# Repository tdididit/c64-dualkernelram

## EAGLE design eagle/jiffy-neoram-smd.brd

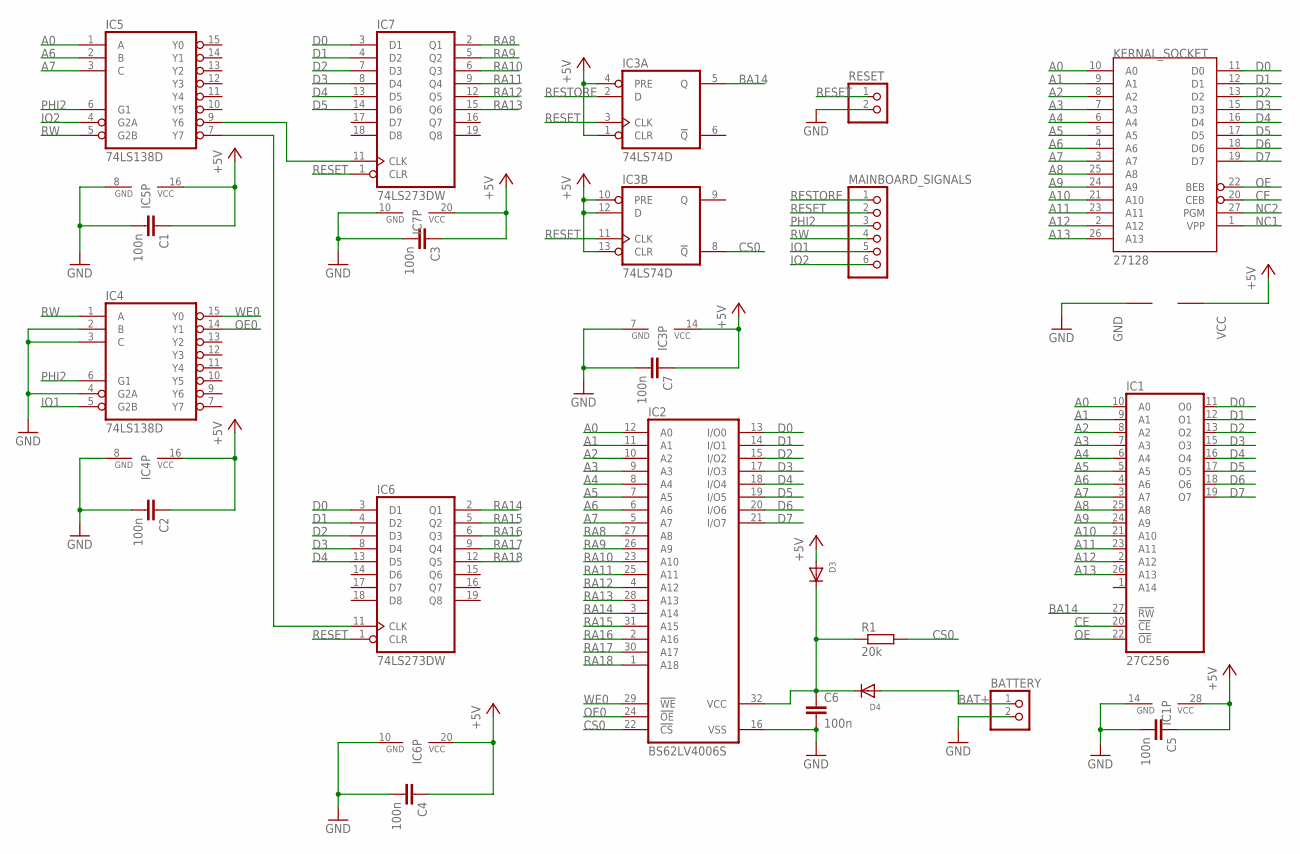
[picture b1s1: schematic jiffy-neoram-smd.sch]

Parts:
BATTERY: HEADER-1X2ROUND; 1X02_ROUND
C1, C2, C3, C4, C5, C6, C7: 100n; C0603
D3, D4: DIODESOD-323F; SOD-323F
IC1: 27C256; DIL28
IC2: BS62LV4006S; SOP-32
IC3: 74LS74D; SO14
IC4, IC5: 74LS138D; SO16
IC6, IC7: 74LS273DW; SO20W
KERNAL_SOCKET: DIL28-6
MAINBOARD_SIGNALS: HEADER-1X6ROUND; 1X06_ROUND
R1: 20k; R0603
RESET: HEADER-1X2ROUND; 1X02_ROUND

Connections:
+5V: C1.1, C2.1, C3.1, C4.1, C5.1, C7.1, D3.A, IC1.28 (VCC), IC3.1 (CLR), IC3.4 (PRE), IC3.10 (PRE), IC3.12 (D), IC3.13 (CLR), IC3.14 (VCC), IC4.16 (VCC), IC5.16 (VCC), IC6.20 (VCC), IC7.20 (VCC), KERNAL_SOCKET.28 (VCC)
A0: IC1.10 (A0), IC2.12 (A0), IC5.1 (A), KERNAL_SOCKET.10 (A0)
A1: IC1.9 (A1), IC2.11 (A1), KERNAL_SOCKET.9 (A1)
A2: IC1.8 (A2), IC2.10 (A2), KERNAL_SOCKET.8 (A2)
A3: IC1.7 (A3), IC2.9 (A3), KERNAL_SOCKET.7 (A3)
A4: IC1.6 (A4), IC2.8 (A4), KERNAL_SOCKET.6 (A4)
A5: IC1.5 (A5), IC2.7 (A5), KERNAL_SOCKET.5 (A5)
A6: IC1.4 (A6), IC2.6 (A6), IC5.2 (B), KERNAL_SOCKET.4 (A6)
A7: IC1.3 (A7), IC2.5 (A7), IC5.3 (C), KERNAL_SOCKET.3 (A7)
A8: IC1.25 (A8), KERNAL_SOCKET.25 (A8)
A9: IC1.24 (A9), KERNAL_SOCKET.24 (A9)
A10: IC1.21 (A10), KERNAL_SOCKET.21 (A10)
A11: IC1.23 (A11), KERNAL_SOCKET.23 (A11)
A12: IC1.2 (A12), KERNAL_SOCKET.2 (A12)
A13: IC1.26 (A13), KERNAL_SOCKET.26 (A13)
BA14: IC1.27 (!RW), IC3.5 (Q)
BAT+: BATTERY.1, D4.A
CE: IC1.20 (!CE), KERNAL_SOCKET.20 (CEB)
CS0: IC2.22 (!CS), IC3.8 (!Q), R1.2
D0: IC1.11 (O0), IC2.13 (I/O0), IC6.3 (D1), IC7.3 (D1), KERNAL_SOCKET.11 (D0)
D1: IC1.12 (O1), IC2.14 (I/O1), IC6.4 (D2), IC7.4 (D2), KERNAL_SOCKET.12 (D1)
D2: IC1.13 (O2), IC2.15 (I/O2), IC6.7 (D3), IC7.7 (D3), KERNAL_SOCKET.13 (D2)
D3: IC1.15 (O3), IC2.17 (I/O3), IC6.8 (D4), IC7.8 (D4), KERNAL_SOCKET.15 (D3)
D4: IC1.16 (O4), IC2.18 (I/O4), IC6.13 (D5), IC7.13 (D5), KERNAL_SOCKET.16 (D4)
D5: IC1.17 (O5), IC2.19 (I/O5), IC7.14 (D6), KERNAL_SOCKET.17 (D5)
D6: IC1.18 (O6), IC2.20 (I/O6), KERNAL_SOCKET.18 (D6)
D7: IC1.19 (O7), IC2.21 (I/O7), KERNAL_SOCKET.19 (D7)
GND: BATTERY.2, C1.2, C2.2, C3.2, C4.2, C5.2, C6.2, C7.2, IC1.14 (GND), IC2.16 (VSS), IC3.7 (GND), IC4.2 (B), IC4.3 (C), IC4.4 (G2A), IC4.8 (GND), IC5.8 (GND), IC6.10 (GND), IC7.10 (GND), KERNAL_SOCKET.14 (GND), RESET.2
IO1: IC4.5 (G2B), MAINBOARD_SIGNALS.5
IO2: IC5.4 (G2A), MAINBOARD_SIGNALS.6
unnamed: IC5.9 (Y6), IC7.11 (CLK)
unnamed: IC5.7 (Y7), IC6.11 (CLK)
unnamed: C6.1, D3.C, D4.C, IC2.32 (VCC), R1.1
NC1: KERNAL_SOCKET.1 (VPP)
NC2: KERNAL_SOCKET.27 (PGM)
OE: IC1.22 (!OE), KERNAL_SOCKET.22 (BEB)
OE0: IC2.24 (!OE), IC4.14 (Y1)
PHI2: IC4.6 (G1), IC5.6 (G1), MAINBOARD_SIGNALS.3
RA8: IC2.27 (A8), IC7.2 (Q1)
RA9: IC2.26 (A9), IC7.5 (Q2)
RA10: IC2.23 (A10), IC7.6 (Q3)
RA11: IC2.25 (A11), IC7.9 (Q4)
RA12: IC2.4 (A12), IC7.12 (Q5)
RA13: IC2.28 (A13), IC7.15 (Q6)
RA14: IC2.3 (A14), IC6.2 (Q1)
RA15: IC2.31 (A15), IC6.5 (Q2)
RA16: IC2.2 (A16), IC6.6 (Q3)
RA17: IC2.30 (A17), IC6.9 (Q4)
RA18: IC2.1 (A18), IC6.12 (Q5)
RESET: IC3.3 (CLK), IC3.11 (CLK), IC6.1 (CLR), IC7.1 (CLR), MAINBOARD_SIGNALS.2, RESET.1
RESTORE: IC3.2 (D), MAINBOARD_SIGNALS.1
RW: IC4.1 (A), IC5.5 (G2B), MAINBOARD_SIGNALS.4
WE0: IC2.29 (!WE), IC4.15 (Y0)

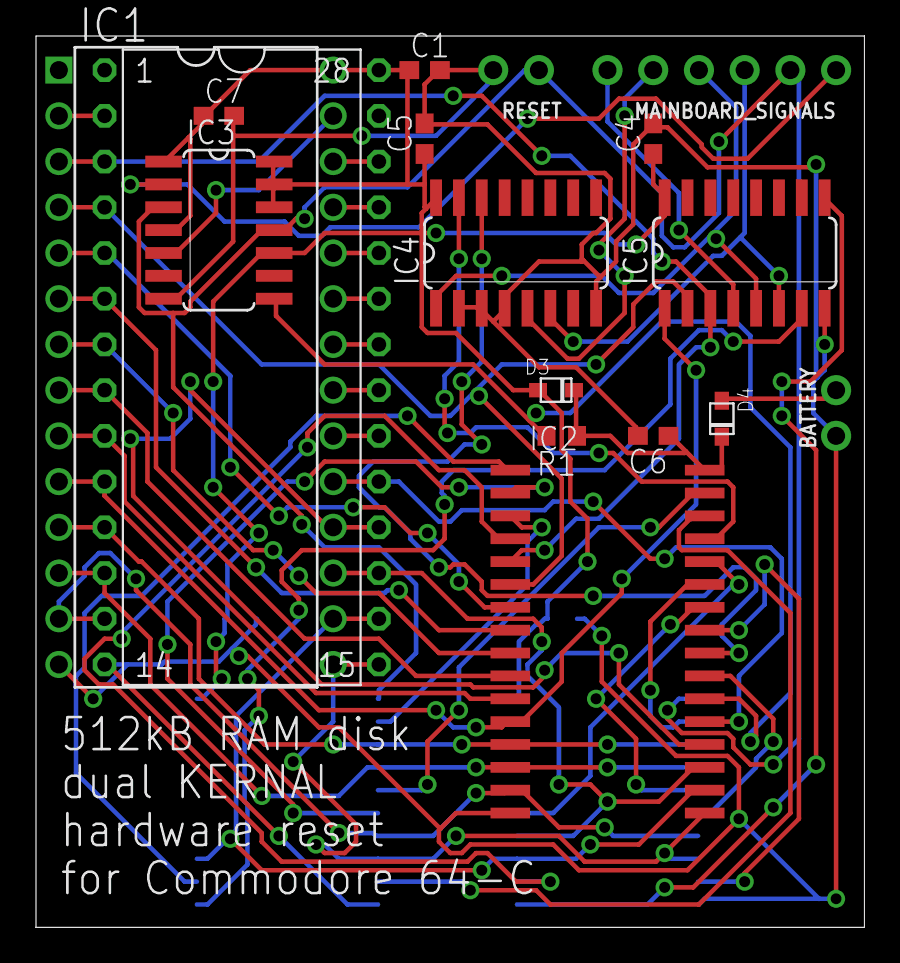
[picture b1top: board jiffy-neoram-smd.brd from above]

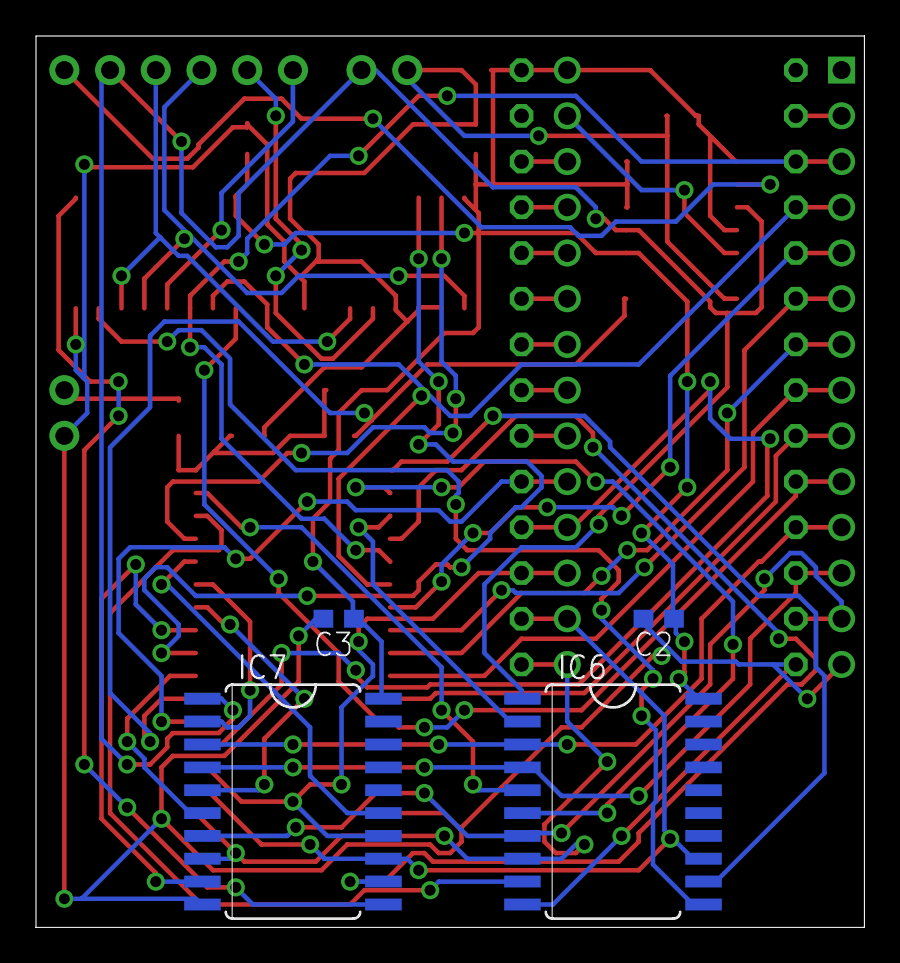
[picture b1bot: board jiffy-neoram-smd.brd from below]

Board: 2 copper layers, 46.0 x 49.5 mm, 21 parts (4 on the bottom side), 51 nets.

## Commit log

2016-04-23 :confetti_ball: Added .gitattributes

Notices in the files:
parts and their libraries:
microbuilder: This work is placed in the public domain, and may be freely used for commercial and non-commercial work with the following conditions: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
